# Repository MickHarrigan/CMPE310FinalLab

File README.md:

# CMPE310FinalLab
Final lab for CMPE 310
Design Requirments/Group Responsibilities
To-Do:https://docs.google.com/document/d/1CQsttLgWNTp7JJfrLSMS7ZLBQpcS6n6CV2k6IQBPOWc/edit?usp=sharing

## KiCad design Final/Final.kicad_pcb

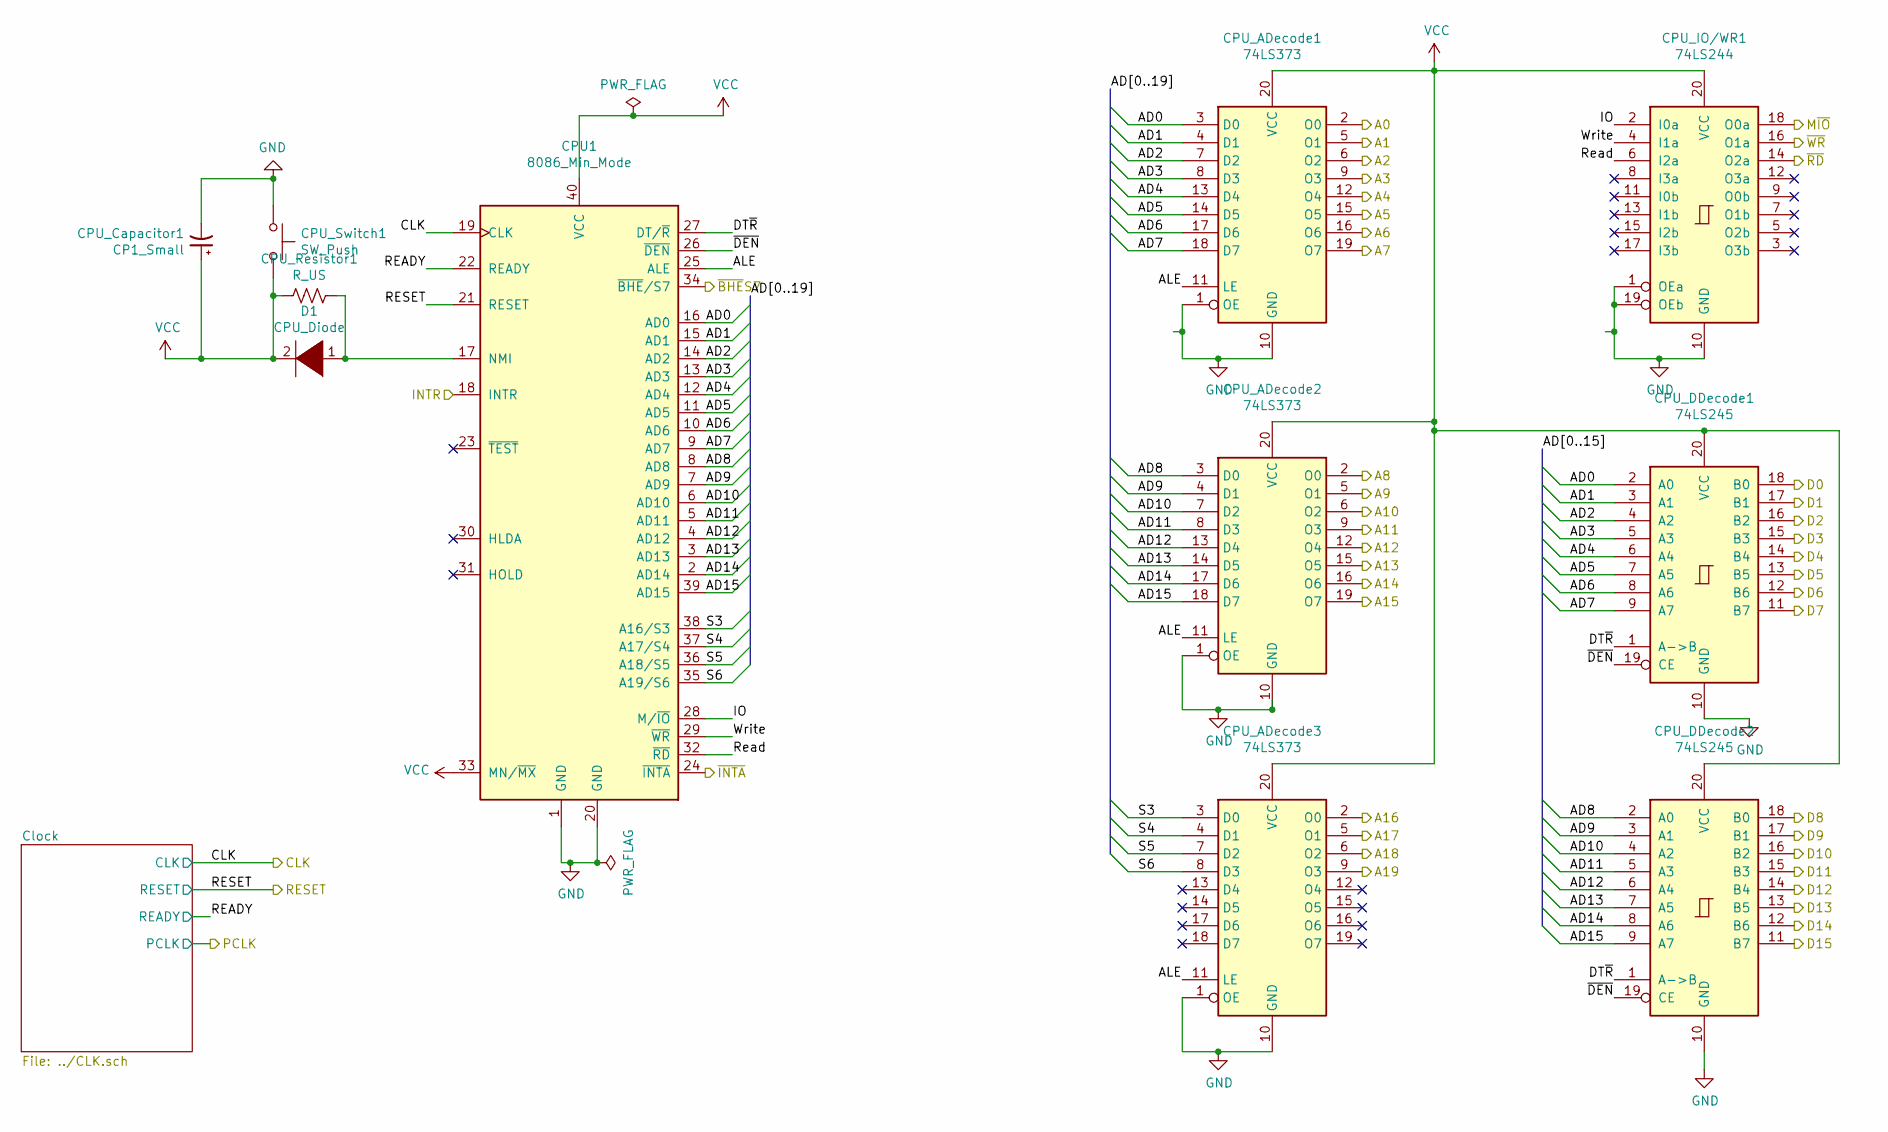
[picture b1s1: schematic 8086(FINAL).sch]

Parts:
CPU1: 8086_Min_Mode; DIP-40_W15.24mm
CPU_ADecode1, CPU_ADecode2, CPU_ADecode3: 74LS373
CPU_Capacitor1: CP1_Small
CPU_DDecode1, CPU_DDecode2: 74LS245
CPU_IO/WR1: 74LS244
CPU_Resistor1: R_US
CPU_Switch1: SW_Push
D1: CPU_Diode

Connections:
/8086/AD0: CPU1.16 (AD0), CPU_ADecode1.3 (D0), CPU_DDecode1.2 (A0)
/8086/AD1: CPU1.15 (AD1), CPU_ADecode1.4 (D1), CPU_DDecode1.3 (A1)
/8086/AD2: CPU1.14 (AD2), CPU_ADecode1.7 (D2), CPU_DDecode1.4 (A2)
/8086/AD3: CPU1.13 (AD3), CPU_ADecode1.8 (D3), CPU_DDecode1.5 (A3)
/8086/AD4: CPU1.12 (AD4), CPU_ADecode1.13 (D4), CPU_DDecode1.6 (A4)
/8086/AD5: CPU1.11 (AD5), CPU_ADecode1.14 (D5), CPU_DDecode1.7 (A5)
/8086/AD6: CPU1.10 (AD6), CPU_ADecode1.17 (D6), CPU_DDecode1.8 (A6)
/8086/AD7: CPU1.9 (AD7), CPU_ADecode1.18 (D7), CPU_DDecode1.9 (A7)
/8086/AD8: CPU1.8 (AD8), CPU_ADecode2.3 (D0), CPU_DDecode2.2 (A0)
/8086/AD9: CPU1.7 (AD9), CPU_ADecode2.4 (D1), CPU_DDecode2.3 (A1)
/8086/AD10: CPU1.6 (AD10), CPU_ADecode2.7 (D2), CPU_DDecode2.4 (A2)
/8086/AD11: CPU1.5 (AD11), CPU_ADecode2.8 (D3), CPU_DDecode2.5 (A3)
/8086/AD12: CPU1.4 (AD12), CPU_ADecode2.13 (D4), CPU_DDecode2.6 (A4)
/8086/AD13: CPU1.3 (AD13), CPU_ADecode2.14 (D5), CPU_DDecode2.7 (A5)
/8086/AD14: CPU1.2 (AD14), CPU_ADecode2.17 (D6), CPU_DDecode2.8 (A6)
/8086/AD15: CPU1.39 (AD15), CPU_ADecode2.18 (D7), CPU_DDecode2.9 (A7)
/8086/ALE: CPU1.25 (ALE), CPU_ADecode1.11 (LE), CPU_ADecode2.11 (LE), CPU_ADecode3.11 (LE)
/8086/DT~R: CPU1.27 (DT/~R~), CPU_DDecode1.1 (A->B), CPU_DDecode2.1 (A->B)
/8086/IO: CPU1.28 (M/~IO~), CPU_IO/WR1.2 (I0a)
/8086/READY: CPU1.22 (READY); also elsewhere on the board
/8086/Read: CPU1.32 (~RD~), CPU_IO/WR1.6 (I2a)
/8086/S3: CPU1.38 (A16/S3), CPU_ADecode3.3 (D0)
/8086/S4: CPU1.37 (A17/S4), CPU_ADecode3.4 (D1)
/8086/S5: CPU1.36 (A18/S5), CPU_ADecode3.7 (D2)
/8086/S6: CPU1.35 (A19/S6), CPU_ADecode3.8 (D3)
/8086/Write: CPU1.29 (~WR~), CPU_IO/WR1.4 (I1a)
/8086/~DEN: CPU1.26 (~DEN~), CPU_DDecode1.19 (CE), CPU_DDecode2.19 (CE)
/A0: CPU_ADecode1.2 (O0); also elsewhere on the board
/A1: CPU_ADecode1.5 (O1); also elsewhere on the board
/A2: CPU_ADecode1.6 (O2); also elsewhere on the board
/A3: CPU_ADecode1.9 (O3); also elsewhere on the board
/A4: CPU_ADecode1.12 (O4); also elsewhere on the board
/A5: CPU_ADecode1.15 (O5); also elsewhere on the board
/A6: CPU_ADecode1.16 (O6); also elsewhere on the board
/A7: CPU_ADecode1.19 (O7); also elsewhere on the board
/A8: CPU_ADecode2.2 (O0); also elsewhere on the board
/A9: CPU_ADecode2.5 (O1); also elsewhere on the board
/A10: CPU_ADecode2.6 (O2); also elsewhere on the board
/A11: CPU_ADecode2.9 (O3); also elsewhere on the board
/A12: CPU_ADecode2.12 (O4); also elsewhere on the board
/A13: CPU_ADecode2.15 (O5); also elsewhere on the board
/A14: CPU_ADecode2.16 (O6); also elsewhere on the board
/A15: CPU_ADecode2.19 (O7); also elsewhere on the board
/A16: CPU_ADecode3.2 (O0); also elsewhere on the board
/A17: CPU_ADecode3.5 (O1); also elsewhere on the board
/A18: CPU_ADecode3.6 (O2); also elsewhere on the board
/A19: CPU_ADecode3.9 (O3); also elsewhere on the board
/CLK: CPU1.19 (CLK); also elsewhere on the board
/D0: CPU_DDecode1.18 (B0); also elsewhere on the board
/D1: CPU_DDecode1.17 (B1); also elsewhere on the board
/D2: CPU_DDecode1.16 (B2); also elsewhere on the board
/D3: CPU_DDecode1.15 (B3); also elsewhere on the board
/D4: CPU_DDecode1.14 (B4); also elsewhere on the board
/D5: CPU_DDecode1.13 (B5); also elsewhere on the board
/D6: CPU_DDecode1.12 (B6); also elsewhere on the board
/D7: CPU_DDecode1.11 (B7); also elsewhere on the board
/D8: CPU_DDecode2.18 (B0); also elsewhere on the board
/D9: CPU_DDecode2.17 (B1); also elsewhere on the board
/D10: CPU_DDecode2.16 (B2); also elsewhere on the board
/D11: CPU_DDecode2.15 (B3); also elsewhere on the board
/D12: CPU_DDecode2.14 (B4); also elsewhere on the board
/D13: CPU_DDecode2.13 (B5); also elsewhere on the board
/D14: CPU_DDecode2.12 (B6); also elsewhere on the board
/D15: CPU_DDecode2.11 (B7); also elsewhere on the board
/INTR: CPU1.18 (INTR); also elsewhere on the board
/M~IO: CPU_IO/WR1.18 (O0a); also elsewhere on the board
/RESET: CPU1.21 (RESET); also elsewhere on the board
/~BHE~S7: CPU1.34 (~BHE~/S7); also elsewhere on the board
/~INTA: CPU1.24 (~INTA~); also elsewhere on the board
/~RD: CPU_IO/WR1.14 (O2a); also elsewhere on the board
/~WR: CPU_IO/WR1.16 (O1a); also elsewhere on the board
GND: CPU1.1 (GND), CPU1.20 (GND), CPU_ADecode1.1 (OE), CPU_ADecode1.10 (GND), CPU_ADecode2.1 (OE), CPU_ADecode2.10 (GND), CPU_ADecode3.1 (OE), CPU_ADecode3.10 (GND), CPU_Capacitor1.2, CPU_DDecode1.10 (GND), CPU_DDecode2.10 (GND), CPU_IO/WR1.1 (OEa), CPU_IO/WR1.10 (GND), CPU_IO/WR1.19 (OEb), CPU_Switch1.1; also elsewhere on the board
unnamed: CPU1.17 (NMI), CPU_Resistor1.1, D1.1 (K)
VCC: CPU1.33 (MN/~MX~), CPU1.40 (VCC), CPU_ADecode1.20 (VCC), CPU_ADecode2.20 (VCC), CPU_ADecode3.20 (VCC), CPU_Capacitor1.1, CPU_DDecode1.20 (VCC), CPU_DDecode2.20 (VCC), CPU_IO/WR1.20 (VCC), CPU_Resistor1.2, CPU_Switch1.2, D1.2 (A); also elsewhere on the board

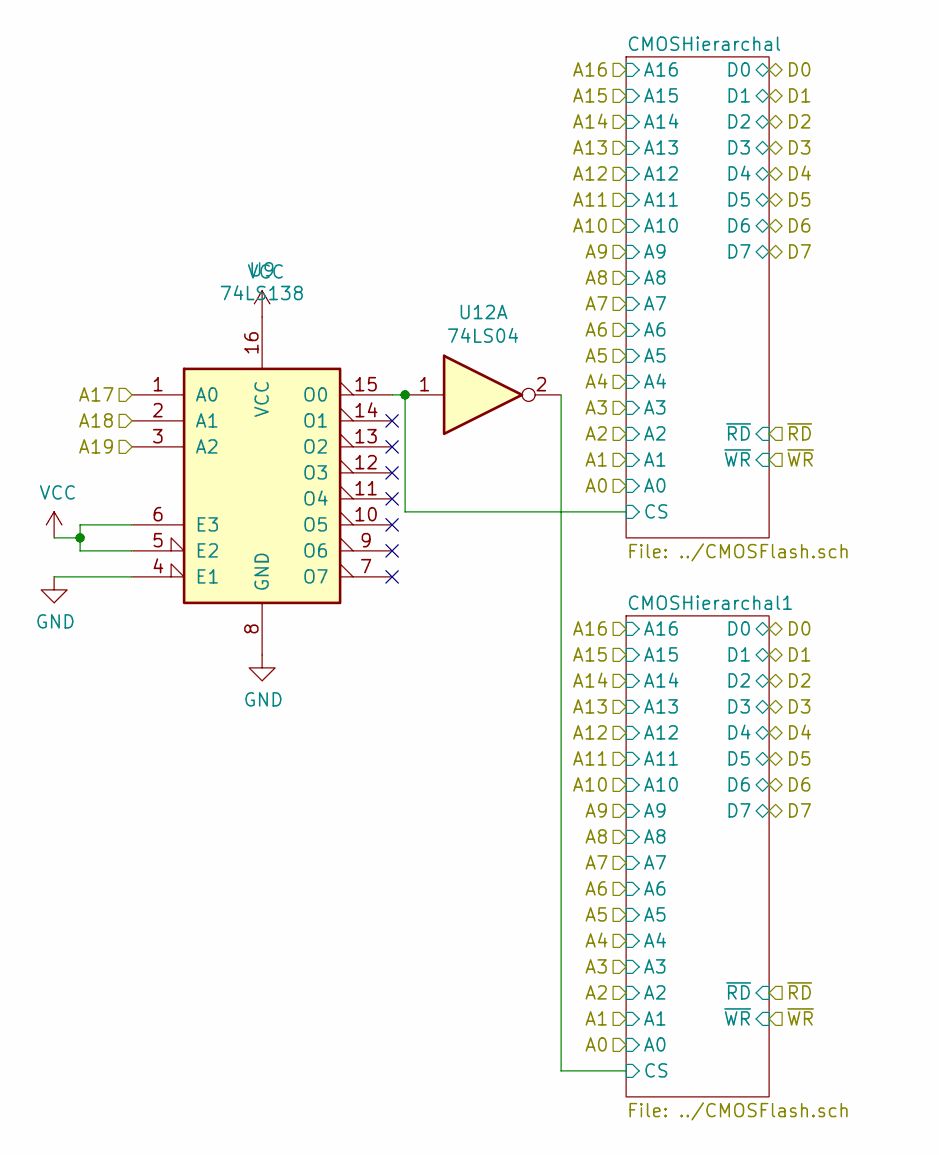
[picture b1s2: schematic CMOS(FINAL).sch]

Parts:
U9: 74LS138
U12: 74LS04

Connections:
/A17: U9.1 (A0); also elsewhere on the board
/A18: U9.2 (A1); also elsewhere on the board
/A19: U9.3 (A2); also elsewhere on the board
/CMOS Flash/CMOSHierarchal1/CS: U12.2; also elsewhere on the board
/CMOS Flash/CMOSHierarchal/CS: U9.15 (O0), U12.1; also elsewhere on the board
GND: U9.4 (E1), U9.8 (GND); also elsewhere on the board
VCC: U9.5 (E2), U9.6 (E3), U9.16 (VCC); also elsewhere on the board

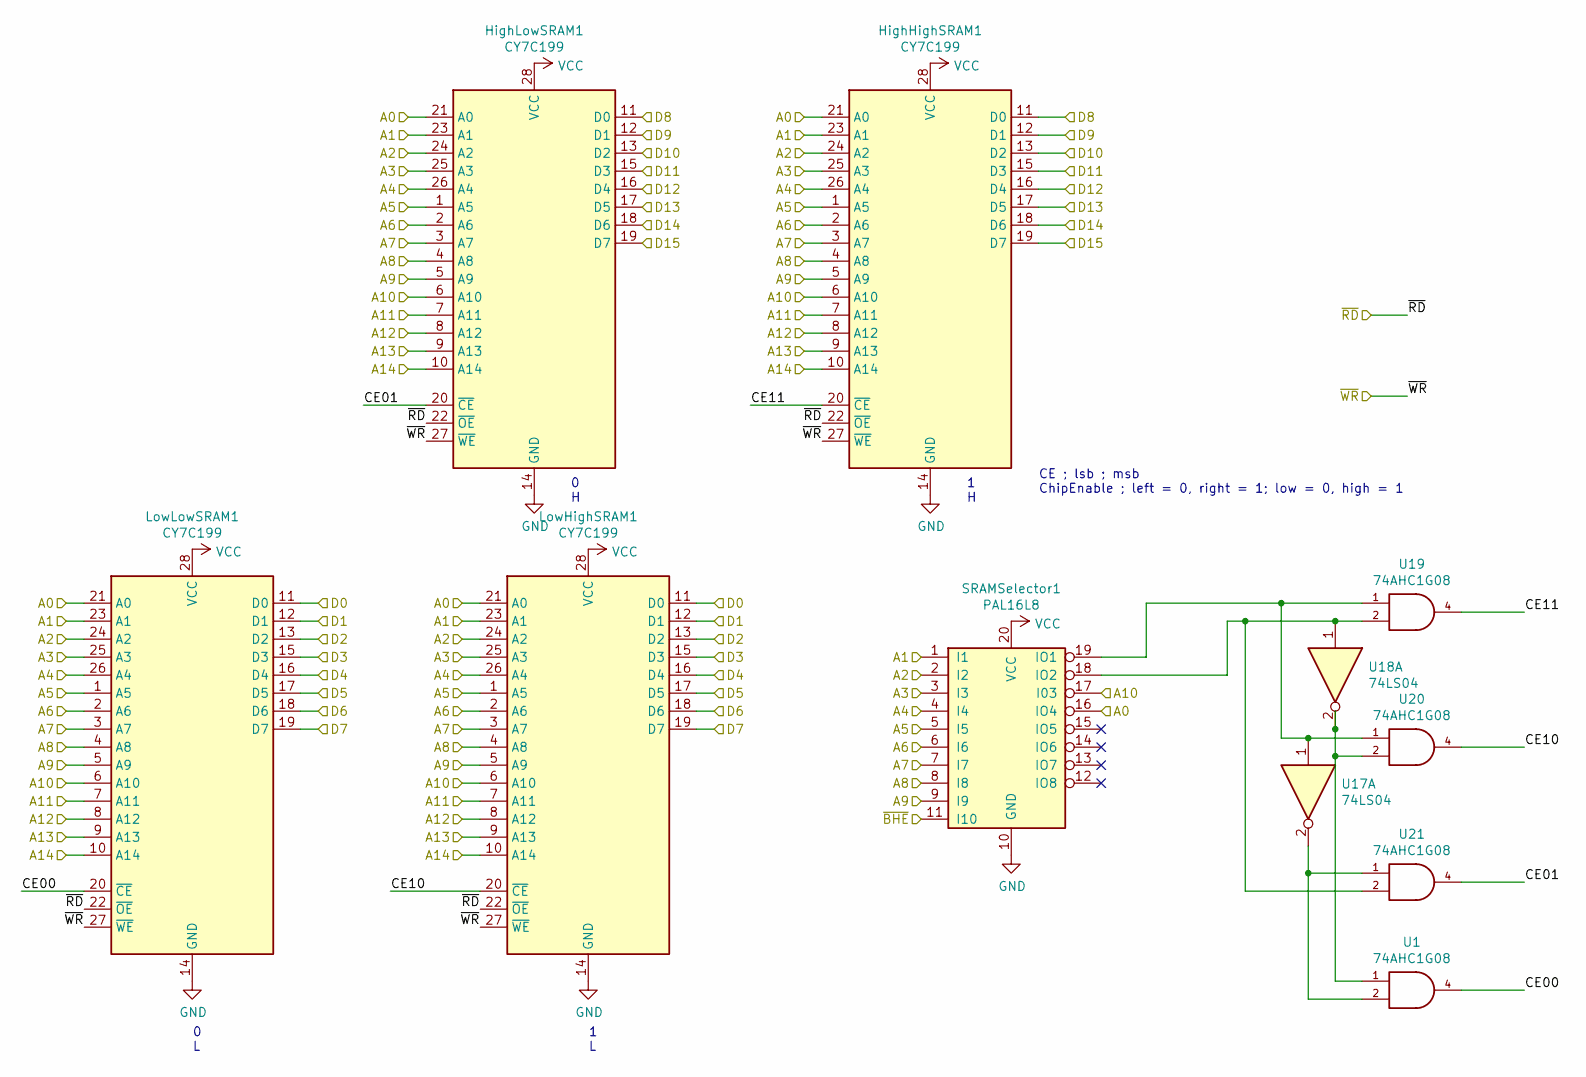
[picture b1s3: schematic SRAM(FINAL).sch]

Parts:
HighHighSRAM1: CY7C199
HighLowSRAM1: CY7C199
LowHighSRAM1: CY7C199
LowLowSRAM1: CY7C199
SRAMSelector1: PAL16L8
U1, U19, U20, U21: 74AHC1G08
U17, U18: 74LS04

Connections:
/A0: HighHighSRAM1.21 (A0), HighLowSRAM1.21 (A0), LowHighSRAM1.21 (A0), LowLowSRAM1.21 (A0), SRAMSelector1.16 (IO4); also elsewhere on the board
/A1: HighHighSRAM1.23 (A1), HighLowSRAM1.23 (A1), LowHighSRAM1.23 (A1), LowLowSRAM1.23 (A1), SRAMSelector1.1 (I1); also elsewhere on the board
/A2: HighHighSRAM1.24 (A2), HighLowSRAM1.24 (A2), LowHighSRAM1.24 (A2), LowLowSRAM1.24 (A2), SRAMSelector1.2 (I2); also elsewhere on the board
/A3: HighHighSRAM1.25 (A3), HighLowSRAM1.25 (A3), LowHighSRAM1.25 (A3), LowLowSRAM1.25 (A3), SRAMSelector1.3 (I3); also elsewhere on the board
/A4: HighHighSRAM1.26 (A4), HighLowSRAM1.26 (A4), LowHighSRAM1.26 (A4), LowLowSRAM1.26 (A4), SRAMSelector1.4 (I4); also elsewhere on the board
/A5: HighHighSRAM1.1 (A5), HighLowSRAM1.1 (A5), LowHighSRAM1.1 (A5), LowLowSRAM1.1 (A5), SRAMSelector1.5 (I5); also elsewhere on the board
/A6: HighHighSRAM1.2 (A6), HighLowSRAM1.2 (A6), LowHighSRAM1.2 (A6), LowLowSRAM1.2 (A6), SRAMSelector1.6 (I6); also elsewhere on the board
/A7: HighHighSRAM1.3 (A7), HighLowSRAM1.3 (A7), LowHighSRAM1.3 (A7), LowLowSRAM1.3 (A7), SRAMSelector1.7 (I7); also elsewhere on the board
/A8: HighHighSRAM1.4 (A8), HighLowSRAM1.4 (A8), LowHighSRAM1.4 (A8), LowLowSRAM1.4 (A8), SRAMSelector1.8 (I8); also elsewhere on the board
/A9: HighHighSRAM1.5 (A9), HighLowSRAM1.5 (A9), LowHighSRAM1.5 (A9), LowLowSRAM1.5 (A9), SRAMSelector1.9 (I9); also elsewhere on the board
/A10: HighHighSRAM1.6 (A10), HighLowSRAM1.6 (A10), LowHighSRAM1.6 (A10), LowLowSRAM1.6 (A10), SRAMSelector1.17 (I03); also elsewhere on the board
/A11: HighHighSRAM1.7 (A11), HighLowSRAM1.7 (A11), LowHighSRAM1.7 (A11), LowLowSRAM1.7 (A11); also elsewhere on the board
/A12: HighHighSRAM1.8 (A12), HighLowSRAM1.8 (A12), LowHighSRAM1.8 (A12), LowLowSRAM1.8 (A12); also elsewhere on the board
/A13: HighHighSRAM1.9 (A13), HighLowSRAM1.9 (A13), LowHighSRAM1.9 (A13), LowLowSRAM1.9 (A13); also elsewhere on the board
/A14: HighHighSRAM1.10 (A14), HighLowSRAM1.10 (A14), LowHighSRAM1.10 (A14), LowLowSRAM1.10 (A14); also elsewhere on the board
/D0: LowHighSRAM1.11 (D0), LowLowSRAM1.11 (D0); also elsewhere on the board
/D1: LowHighSRAM1.12 (D1), LowLowSRAM1.12 (D1); also elsewhere on the board
/D2: LowHighSRAM1.13 (D2), LowLowSRAM1.13 (D2); also elsewhere on the board
/D3: LowHighSRAM1.15 (D3), LowLowSRAM1.15 (D3); also elsewhere on the board
/D4: LowHighSRAM1.16 (D4), LowLowSRAM1.16 (D4); also elsewhere on the board
/D5: LowHighSRAM1.17 (D5), LowLowSRAM1.17 (D5); also elsewhere on the board
/D6: LowHighSRAM1.18 (D6), LowLowSRAM1.18 (D6); also elsewhere on the board
/D7: LowHighSRAM1.19 (D7), LowLowSRAM1.19 (D7); also elsewhere on the board
/D8: HighHighSRAM1.11 (D0), HighLowSRAM1.11 (D0); also elsewhere on the board
/D9: HighHighSRAM1.12 (D1), HighLowSRAM1.12 (D1); also elsewhere on the board
/D10: HighHighSRAM1.13 (D2), HighLowSRAM1.13 (D2); also elsewhere on the board
/D11: HighHighSRAM1.15 (D3), HighLowSRAM1.15 (D3); also elsewhere on the board
/D12: HighHighSRAM1.16 (D4), HighLowSRAM1.16 (D4); also elsewhere on the board
/D13: HighHighSRAM1.17 (D5), HighLowSRAM1.17 (D5); also elsewhere on the board
/D14: HighHighSRAM1.18 (D6), HighLowSRAM1.18 (D6); also elsewhere on the board
/D15: HighHighSRAM1.19 (D7), HighLowSRAM1.19 (D7); also elsewhere on the board
/SRAM/CE00: LowLowSRAM1.20 (~CE~), U1.4
/SRAM/CE01: HighLowSRAM1.20 (~CE~), U21.4
/SRAM/CE10: LowHighSRAM1.20 (~CE~), U20.4
/SRAM/CE11: HighHighSRAM1.20 (~CE~), U19.4
/~BHE~S7: SRAMSelector1.11 (I10); also elsewhere on the board
/~RD: HighHighSRAM1.22 (~OE~), HighLowSRAM1.22 (~OE~), LowHighSRAM1.22 (~OE~), LowLowSRAM1.22 (~OE~); also elsewhere on the board
/~WR: HighHighSRAM1.27 (~WE~), HighLowSRAM1.27 (~WE~), LowHighSRAM1.27 (~WE~), LowLowSRAM1.27 (~WE~); also elsewhere on the board
GND: HighHighSRAM1.14 (GND), HighLowSRAM1.14 (GND), LowHighSRAM1.14 (GND), LowLowSRAM1.14 (GND), SRAMSelector1.10 (GND), U1.3 (GND), U19.3 (GND), U20.3 (GND), U21.3 (GND); also elsewhere on the board
unnamed: SRAMSelector1.18 (IO2), U18.1, U19.2, U21.2
unnamed: SRAMSelector1.19 (IO1), U17.1, U19.1, U20.1
unnamed: U1.1, U18.2, U20.2
unnamed: U1.2, U17.2, U21.1
VCC: HighHighSRAM1.28 (VCC), HighLowSRAM1.28 (VCC), LowHighSRAM1.28 (VCC), LowLowSRAM1.28 (VCC), SRAMSelector1.20 (VCC); also elsewhere on the board

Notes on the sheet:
0 L
1 L
0 H
1 H
CE ; lsb ; msb ChipEnable ; left = 0, right = 1; low = 0, high = 1

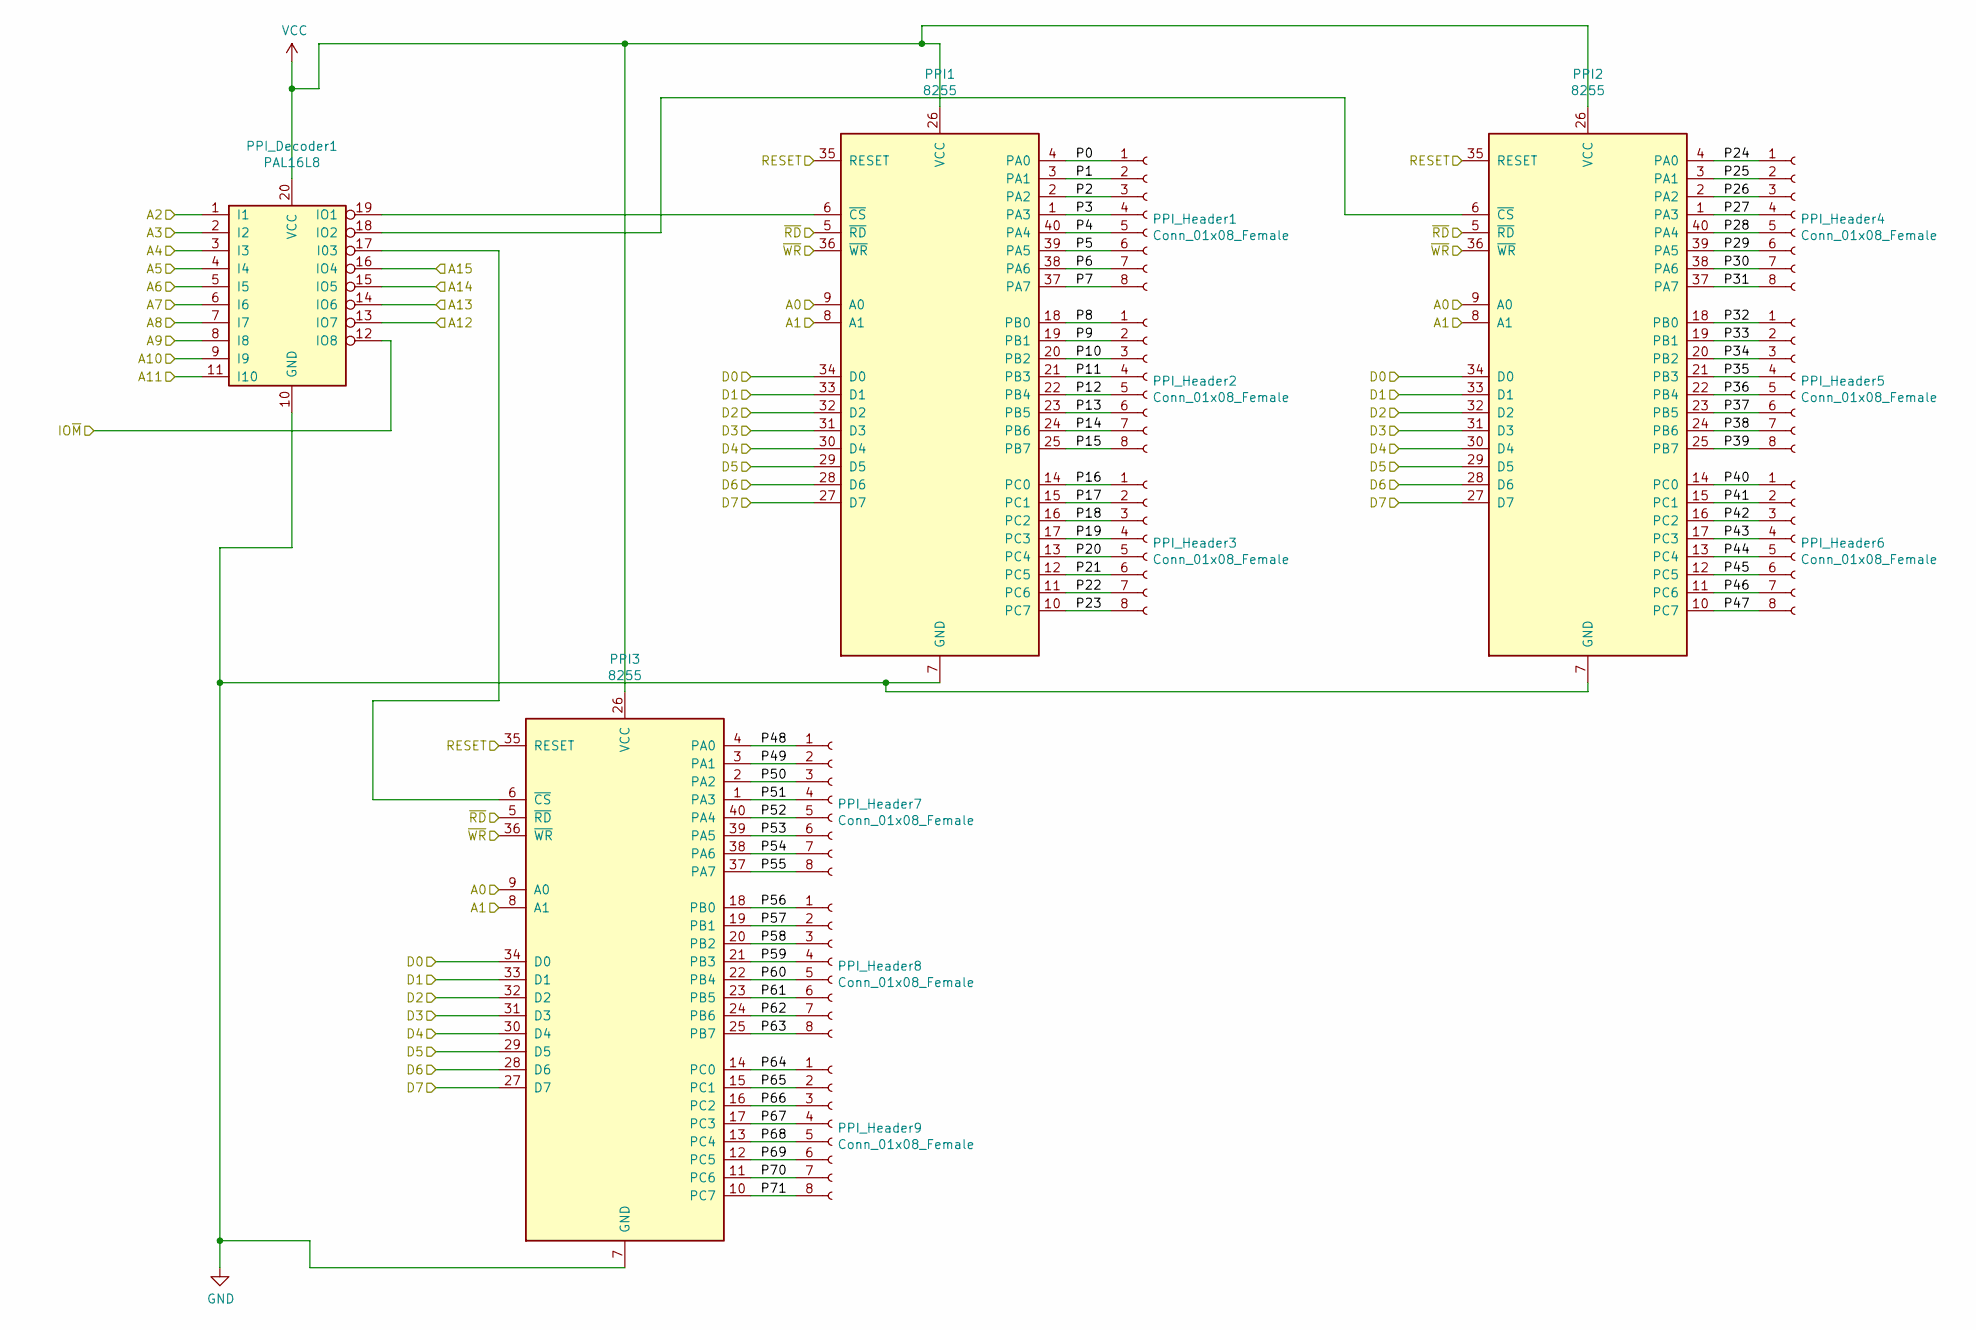
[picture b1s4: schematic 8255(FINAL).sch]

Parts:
PPI1, PPI2, PPI3: 8255; DIP-40_W15.24mm
PPI_Decoder1: PAL16L8
PPI_Header1, PPI_Header2, PPI_Header3, PPI_Header4, PPI_Header5, PPI_Header6, PPI_Header7, PPI_Header8, PPI_Header9: Conn_01x08_Female

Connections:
/8255/P0: PPI1.4 (PA0), PPI_Header1.1
/8255/P1: PPI1.3 (PA1), PPI_Header1.2
/8255/P2: PPI1.2 (PA2), PPI_Header1.3
/8255/P3: PPI1.1 (PA3), PPI_Header1.4
/8255/P4: PPI1.40 (PA4), PPI_Header1.5
/8255/P5: PPI1.39 (PA5), PPI_Header1.6
/8255/P6: PPI1.38 (PA6), PPI_Header1.7
/8255/P7: PPI1.37 (PA7), PPI_Header1.8
/8255/P8: PPI1.18 (PB0), PPI_Header2.1
/8255/P9: PPI1.19 (PB1), PPI_Header2.2
/8255/P10: PPI1.20 (PB2), PPI_Header2.3
/8255/P11: PPI1.21 (PB3), PPI_Header2.4
/8255/P12: PPI1.22 (PB4), PPI_Header2.5
/8255/P13: PPI1.23 (PB5), PPI_Header2.6
/8255/P14: PPI1.24 (PB6), PPI_Header2.7
/8255/P15: PPI1.25 (PB7), PPI_Header2.8
/8255/P16: PPI1.14 (PC0), PPI_Header3.1
/8255/P17: PPI1.15 (PC1), PPI_Header3.2
/8255/P18: PPI1.16 (PC2), PPI_Header3.3
/8255/P19: PPI1.17 (PC3), PPI_Header3.4
/8255/P20: PPI1.13 (PC4), PPI_Header3.5
/8255/P21: PPI1.12 (PC5), PPI_Header3.6
/8255/P22: PPI1.11 (PC6), PPI_Header3.7
/8255/P23: PPI1.10 (PC7), PPI_Header3.8
/8255/P24: PPI2.4 (PA0), PPI_Header4.1
/8255/P25: PPI2.3 (PA1), PPI_Header4.2
/8255/P26: PPI2.2 (PA2), PPI_Header4.3
/8255/P27: PPI2.1 (PA3), PPI_Header4.4
/8255/P28: PPI2.40 (PA4), PPI_Header4.5
/8255/P29: PPI2.39 (PA5), PPI_Header4.6
/8255/P30: PPI2.38 (PA6), PPI_Header4.7
/8255/P31: PPI2.37 (PA7), PPI_Header4.8
/8255/P32: PPI2.18 (PB0), PPI_Header5.1
/8255/P33: PPI2.19 (PB1), PPI_Header5.2
/8255/P34: PPI2.20 (PB2), PPI_Header5.3
/8255/P35: PPI2.21 (PB3), PPI_Header5.4
/8255/P36: PPI2.22 (PB4), PPI_Header5.5
/8255/P37: PPI2.23 (PB5), PPI_Header5.6
/8255/P38: PPI2.24 (PB6), PPI_Header5.7
/8255/P39: PPI2.25 (PB7), PPI_Header5.8
/8255/P40: PPI2.14 (PC0), PPI_Header6.1
/8255/P41: PPI2.15 (PC1), PPI_Header6.2
/8255/P42: PPI2.16 (PC2), PPI_Header6.3
/8255/P43: PPI2.17 (PC3), PPI_Header6.4
/8255/P44: PPI2.13 (PC4), PPI_Header6.5
/8255/P45: PPI2.12 (PC5), PPI_Header6.6
/8255/P46: PPI2.11 (PC6), PPI_Header6.7
/8255/P47: PPI2.10 (PC7), PPI_Header6.8
/8255/P48: PPI3.4 (PA0), PPI_Header7.1
/8255/P49: PPI3.3 (PA1), PPI_Header7.2
/8255/P50: PPI3.2 (PA2), PPI_Header7.3
/8255/P51: PPI3.1 (PA3), PPI_Header7.4
/8255/P52: PPI3.40 (PA4), PPI_Header7.5
/8255/P53: PPI3.39 (PA5), PPI_Header7.6
/8255/P54: PPI3.38 (PA6), PPI_Header7.7
/8255/P55: PPI3.37 (PA7), PPI_Header7.8
/8255/P56: PPI3.18 (PB0), PPI_Header8.1
/8255/P57: PPI3.19 (PB1), PPI_Header8.2
/8255/P58: PPI3.20 (PB2), PPI_Header8.3
/8255/P59: PPI3.21 (PB3), PPI_Header8.4
/8255/P60: PPI3.22 (PB4), PPI_Header8.5
/8255/P61: PPI3.23 (PB5), PPI_Header8.6
/8255/P62: PPI3.24 (PB6), PPI_Header8.7
/8255/P63: PPI3.25 (PB7), PPI_Header8.8
/8255/P64: PPI3.14 (PC0), PPI_Header9.1
/8255/P65: PPI3.15 (PC1), PPI_Header9.2
/8255/P66: PPI3.16 (PC2), PPI_Header9.3
/8255/P67: PPI3.17 (PC3), PPI_Header9.4
/8255/P68: PPI3.13 (PC4), PPI_Header9.5
/8255/P69: PPI3.12 (PC5), PPI_Header9.6
/8255/P70: PPI3.11 (PC6), PPI_Header9.7
/8255/P71: PPI3.10 (PC7), PPI_Header9.8
/A0: PPI_Decoder1.1 (I1); also elsewhere on the board
/A1: PPI1.9 (A0), PPI2.9 (A0), PPI3.9 (A0); also elsewhere on the board
/A2: PPI1.8 (A1), PPI2.8 (A1), PPI3.8 (A1); also elsewhere on the board
/A3: PPI_Decoder1.2 (I2); also elsewhere on the board
/A4: PPI_Decoder1.3 (I3); also elsewhere on the board
/A5: PPI_Decoder1.4 (I4); also elsewhere on the board
/A6: PPI_Decoder1.5 (I5); also elsewhere on the board
/A7: PPI_Decoder1.6 (I6); also elsewhere on the board
/A8: PPI_Decoder1.8 (I8); also elsewhere on the board
/A9: PPI_Decoder1.7 (I7); also elsewhere on the board
/A10: PPI_Decoder1.9 (I9); also elsewhere on the board
/A11: PPI_Decoder1.11 (I10); also elsewhere on the board
/A12: PPI_Decoder1.13 (IO7); also elsewhere on the board
/A13: PPI_Decoder1.14 (IO6); also elsewhere on the board
/A14: PPI_Decoder1.15 (IO5); also elsewhere on the board
/A15: PPI_Decoder1.16 (IO4); also elsewhere on the board
/D0: PPI1.34 (D0), PPI2.34 (D0), PPI3.34 (D0); also elsewhere on the board
/D1: PPI1.33 (D1), PPI2.33 (D1), PPI3.33 (D1); also elsewhere on the board
/D2: PPI1.32 (D2), PPI2.32 (D2), PPI3.32 (D2); also elsewhere on the board
/D3: PPI1.31 (D3), PPI2.31 (D3), PPI3.31 (D3); also elsewhere on the board
/D4: PPI1.30 (D4), PPI2.30 (D4), PPI3.30 (D4); also elsewhere on the board
/D5: PPI1.29 (D5), PPI2.29 (D5), PPI3.29 (D5); also elsewhere on the board
/D6: PPI1.28 (D6), PPI2.28 (D6), PPI3.28 (D6); also elsewhere on the board
/D7: PPI1.27 (D7), PPI2.27 (D7), PPI3.27 (D7); also elsewhere on the board
/M~IO: PPI_Decoder1.12 (IO8); also elsewhere on the board
/RESET: PPI1.35 (RESET), PPI2.35 (RESET), PPI3.35 (RESET); also elsewhere on the board
/~RD: PPI1.5 (~RD~), PPI2.5 (~RD~), PPI3.5 (~RD~); also elsewhere on the board
/~WR: PPI1.36 (~WR~), PPI2.36 (~WR~), PPI3.36 (~WR~); also elsewhere on the board
GND: PPI1.7 (GND), PPI2.7 (GND), PPI3.7 (GND), PPI_Decoder1.10 (GND); also elsewhere on the board
unnamed: PPI1.6 (~CS~), PPI_Decoder1.19 (IO1)
unnamed: PPI2.6 (~CS~), PPI_Decoder1.18 (IO2)
unnamed: PPI3.6 (~CS~), PPI_Decoder1.17 (I03)
VCC: PPI1.26 (VCC), PPI2.26 (VCC), PPI3.26 (VCC), PPI_Decoder1.20 (VCC); also elsewhere on the board

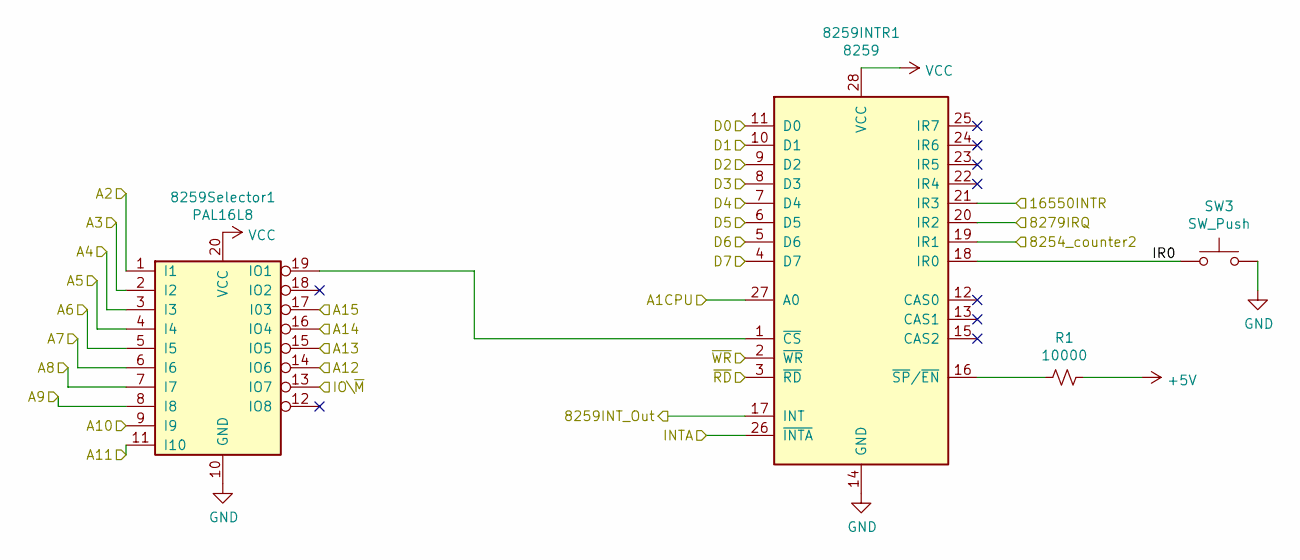
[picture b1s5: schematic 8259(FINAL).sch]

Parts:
8259INTR1: 8259; DIP-28_W15.24mm
8259Selector1: PAL16L8; DIP-20_W7.62mm
R1: 10000
SW3: SW_Push

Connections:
+5V: R1.1; also elsewhere on the board
/8259/IR0: 8259INTR1.18 (IR0), SW3.1
/16550_INTR: 8259INTR1.21 (IR3); also elsewhere on the board
/A1: 8259INTR1.27 (A0); also elsewhere on the board
/A2: 8259Selector1.1 (I1); also elsewhere on the board
/A3: 8259Selector1.2 (I2); also elsewhere on the board
/A4: 8259Selector1.3 (I3); also elsewhere on the board
/A5: 8259Selector1.4 (I4); also elsewhere on the board
/A6: 8259Selector1.5 (I5); also elsewhere on the board
/A7: 8259Selector1.6 (I6); also elsewhere on the board
/A8: 8259Selector1.7 (I7); also elsewhere on the board
/A9: 8259Selector1.8 (I8); also elsewhere on the board
/A10: 8259Selector1.9 (I9); also elsewhere on the board
/A11: 8259Selector1.11 (I10); also elsewhere on the board
/A12: 8259Selector1.14 (IO6); also elsewhere on the board
/A13: 8259Selector1.15 (IO5); also elsewhere on the board
/A14: 8259Selector1.16 (IO4); also elsewhere on the board
/A15: 8259Selector1.17 (I03); also elsewhere on the board
/CNTR2: 8259INTR1.19 (IR1); also elsewhere on the board
/D0: 8259INTR1.11 (D0); also elsewhere on the board
/D1: 8259INTR1.10 (D1); also elsewhere on the board
/D2: 8259INTR1.9 (D2); also elsewhere on the board
/D3: 8259INTR1.8 (D3); also elsewhere on the board
/D4: 8259INTR1.7 (D4); also elsewhere on the board
/D5: 8259INTR1.6 (D5); also elsewhere on the board
/D6: 8259INTR1.5 (D6); also elsewhere on the board
/D7: 8259INTR1.4 (D7); also elsewhere on the board
/INTR: 8259INTR1.17 (INT); also elsewhere on the board
/IRQ: 8259INTR1.20 (IR2); also elsewhere on the board
/M~IO: 8259Selector1.13 (IO7); also elsewhere on the board
/~INTA: 8259INTR1.26 (~INTA~); also elsewhere on the board
/~RD: 8259INTR1.3 (~RD~); also elsewhere on the board
/~WR: 8259INTR1.2 (~WR~); also elsewhere on the board
GND: 8259INTR1.14 (GND), 8259Selector1.10 (GND), SW3.2; also elsewhere on the board
unnamed: 8259INTR1.1 (~CS~), 8259Selector1.19 (IO1)
unnamed: 8259INTR1.16 (~SP~/~EN~), R1.2
VCC: 8259INTR1.28 (VCC), 8259Selector1.20 (VCC); also elsewhere on the board

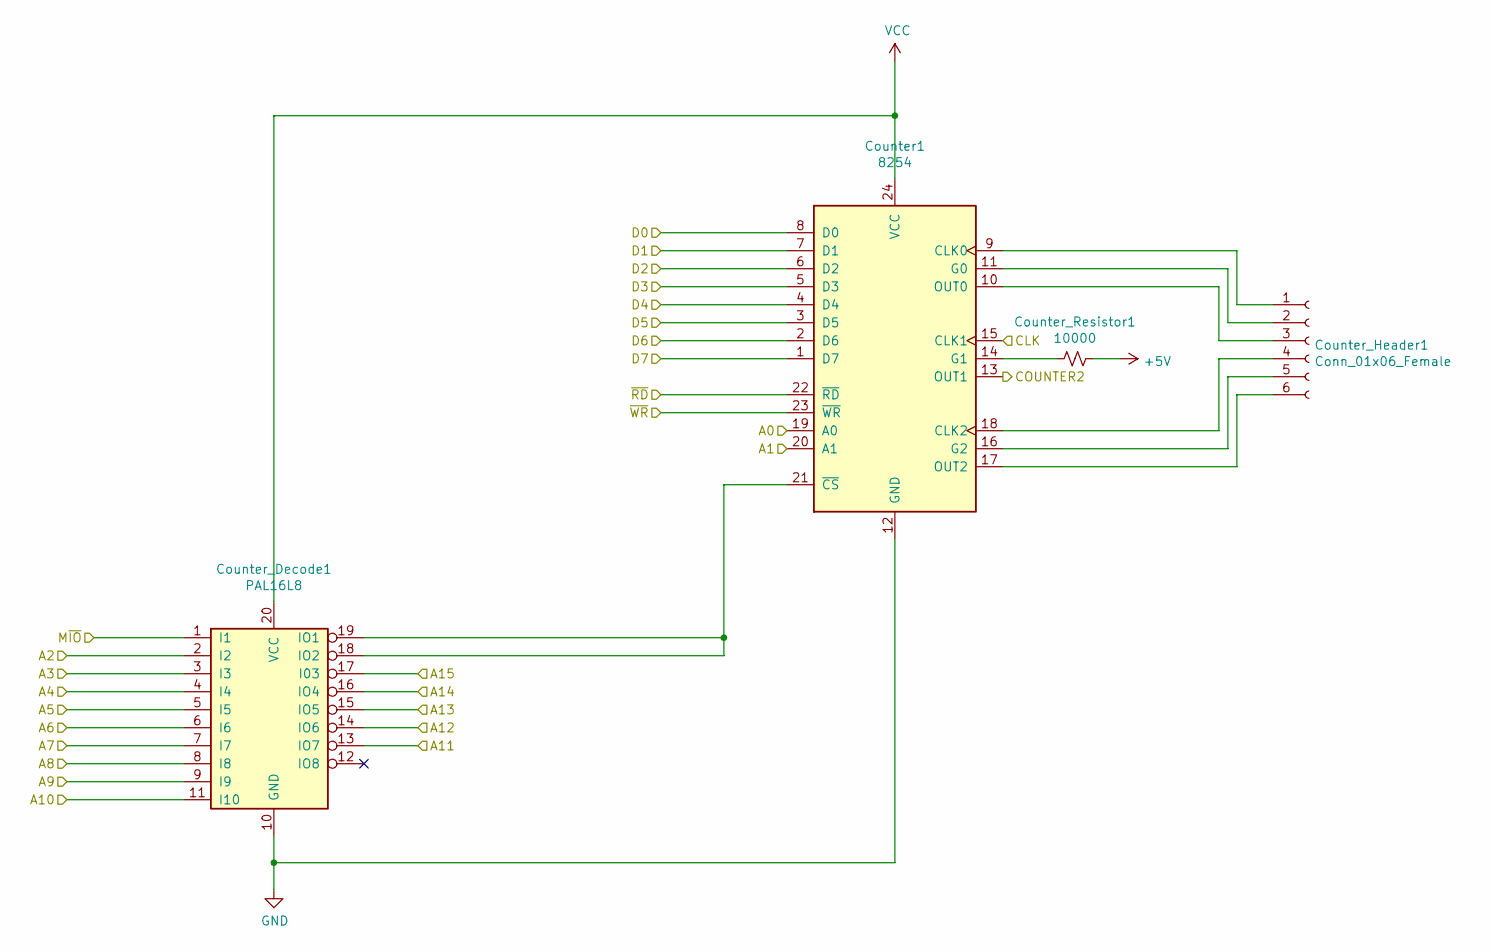
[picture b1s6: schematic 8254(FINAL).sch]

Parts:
Counter1: 8254; DIP-24_W15.24mm
Counter_Decode1: PAL16L8
Counter_Header1: Conn_01x06_Female
Counter_Resistor1: 10000

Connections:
+5V: Counter_Resistor1.1; also elsewhere on the board
/A0: Counter_Decode1.2 (I2); also elsewhere on the board
/A1: Counter1.19 (A0); also elsewhere on the board
/A2: Counter1.20 (A1); also elsewhere on the board
/A3: Counter_Decode1.3 (I3); also elsewhere on the board
/A4: Counter_Decode1.4 (I4); also elsewhere on the board
/A5: Counter_Decode1.5 (I5); also elsewhere on the board
/A6: Counter_Decode1.6 (I6); also elsewhere on the board
/A7: Counter_Decode1.7 (I7); also elsewhere on the board
/A8: Counter_Decode1.8 (I8); also elsewhere on the board
/A9: Counter_Decode1.9 (I9); also elsewhere on the board
/A10: Counter_Decode1.11 (I10); also elsewhere on the board
/A11: Counter_Decode1.13 (IO7); also elsewhere on the board
/A12: Counter_Decode1.14 (IO6); also elsewhere on the board
/A13: Counter_Decode1.15 (IO5); also elsewhere on the board
/A14: Counter_Decode1.16 (IO4); also elsewhere on the board
/A15: Counter_Decode1.17 (I03); also elsewhere on the board
/CLK: Counter1.15 (CLK1); also elsewhere on the board
/CNTR2: Counter1.13 (OUT1); also elsewhere on the board
/D0: Counter1.8 (D0); also elsewhere on the board
/D1: Counter1.7 (D1); also elsewhere on the board
/D2: Counter1.6 (D2); also elsewhere on the board
/D3: Counter1.5 (D3); also elsewhere on the board
/D4: Counter1.4 (D4); also elsewhere on the board
/D5: Counter1.3 (D5); also elsewhere on the board
/D6: Counter1.2 (D6); also elsewhere on the board
/D7: Counter1.1 (D7); also elsewhere on the board
/M~IO: Counter_Decode1.1 (I1); also elsewhere on the board
/~RD: Counter1.22 (~RD~); also elsewhere on the board
/~WR: Counter1.23 (~WR~); also elsewhere on the board
GND: Counter1.12 (GND), Counter_Decode1.10 (GND); also elsewhere on the board
unnamed: Counter1.9 (CLK0), Counter_Header1.1
unnamed: Counter1.10 (OUT0), Counter_Header1.3
unnamed: Counter1.11 (G0), Counter_Header1.2
unnamed: Counter1.14 (G1), Counter_Resistor1.2
unnamed: Counter1.16 (G2), Counter_Header1.5
unnamed: Counter1.17 (OUT2), Counter_Header1.6
unnamed: Counter1.18 (CLK2), Counter_Header1.4
unnamed: Counter1.21 (~CS~), Counter_Decode1.18 (IO2), Counter_Decode1.19 (IO1)
VCC: Counter1.24 (VCC), Counter_Decode1.20 (VCC); also elsewhere on the board
